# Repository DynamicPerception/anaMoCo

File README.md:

anaMoCo Board
=============

The anaMoCo board is the heart of the [AT<sup>2</sup> two-axis analog controller](http://dynamicperception.com/products/at2-motion-controller)
 sold by Dynamic Perception.

This controller supports control of two DC motors from 6-16V at up to 1.2A each axis.

Key Features
------------

- Control up to two DC motor axes
     - 6-16V power input/output
     - Up to 1.2A per axis
- 99% Analog (one final PWM stage)
     - No microcontroller
- Support for input from a two axis, pot-style joystick and two knobs
- Analog damping support
- Cruise control
- Direction inversion
- Locking DC Jacks

License and Copyright
---------------------

anaMoCo and the AT<sup>2</sup> are Copyright (c) 2012-2013 Dynamic Perception LLC.

All files shared under the Creative Commons Attibution-Share-Alike 3.0 License.

anaMoCo and AT<sup>2</sup> names are trademarks of Dynamic Perception LLC.

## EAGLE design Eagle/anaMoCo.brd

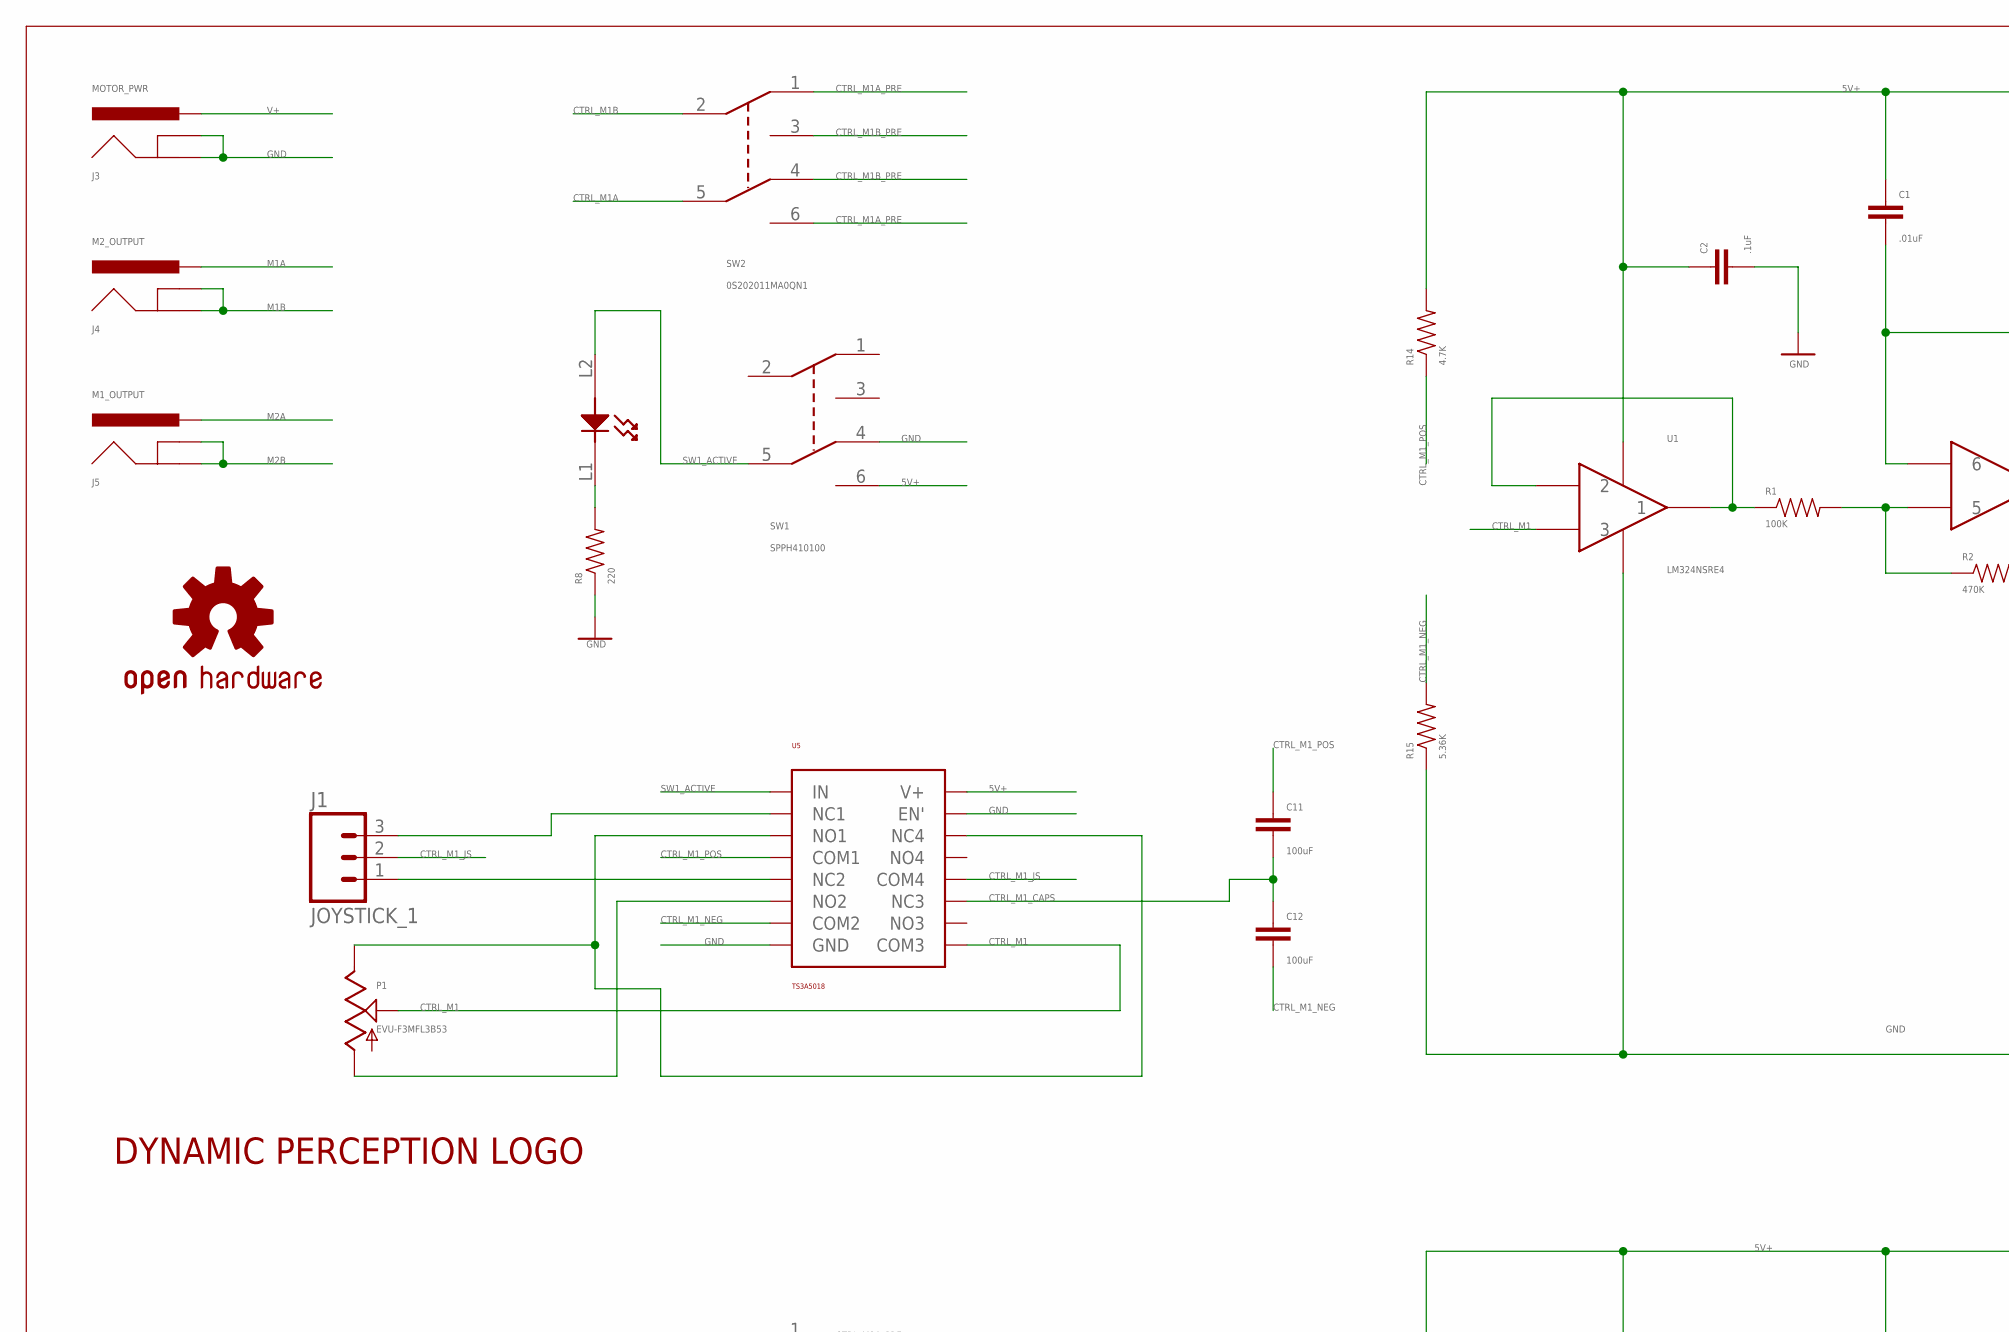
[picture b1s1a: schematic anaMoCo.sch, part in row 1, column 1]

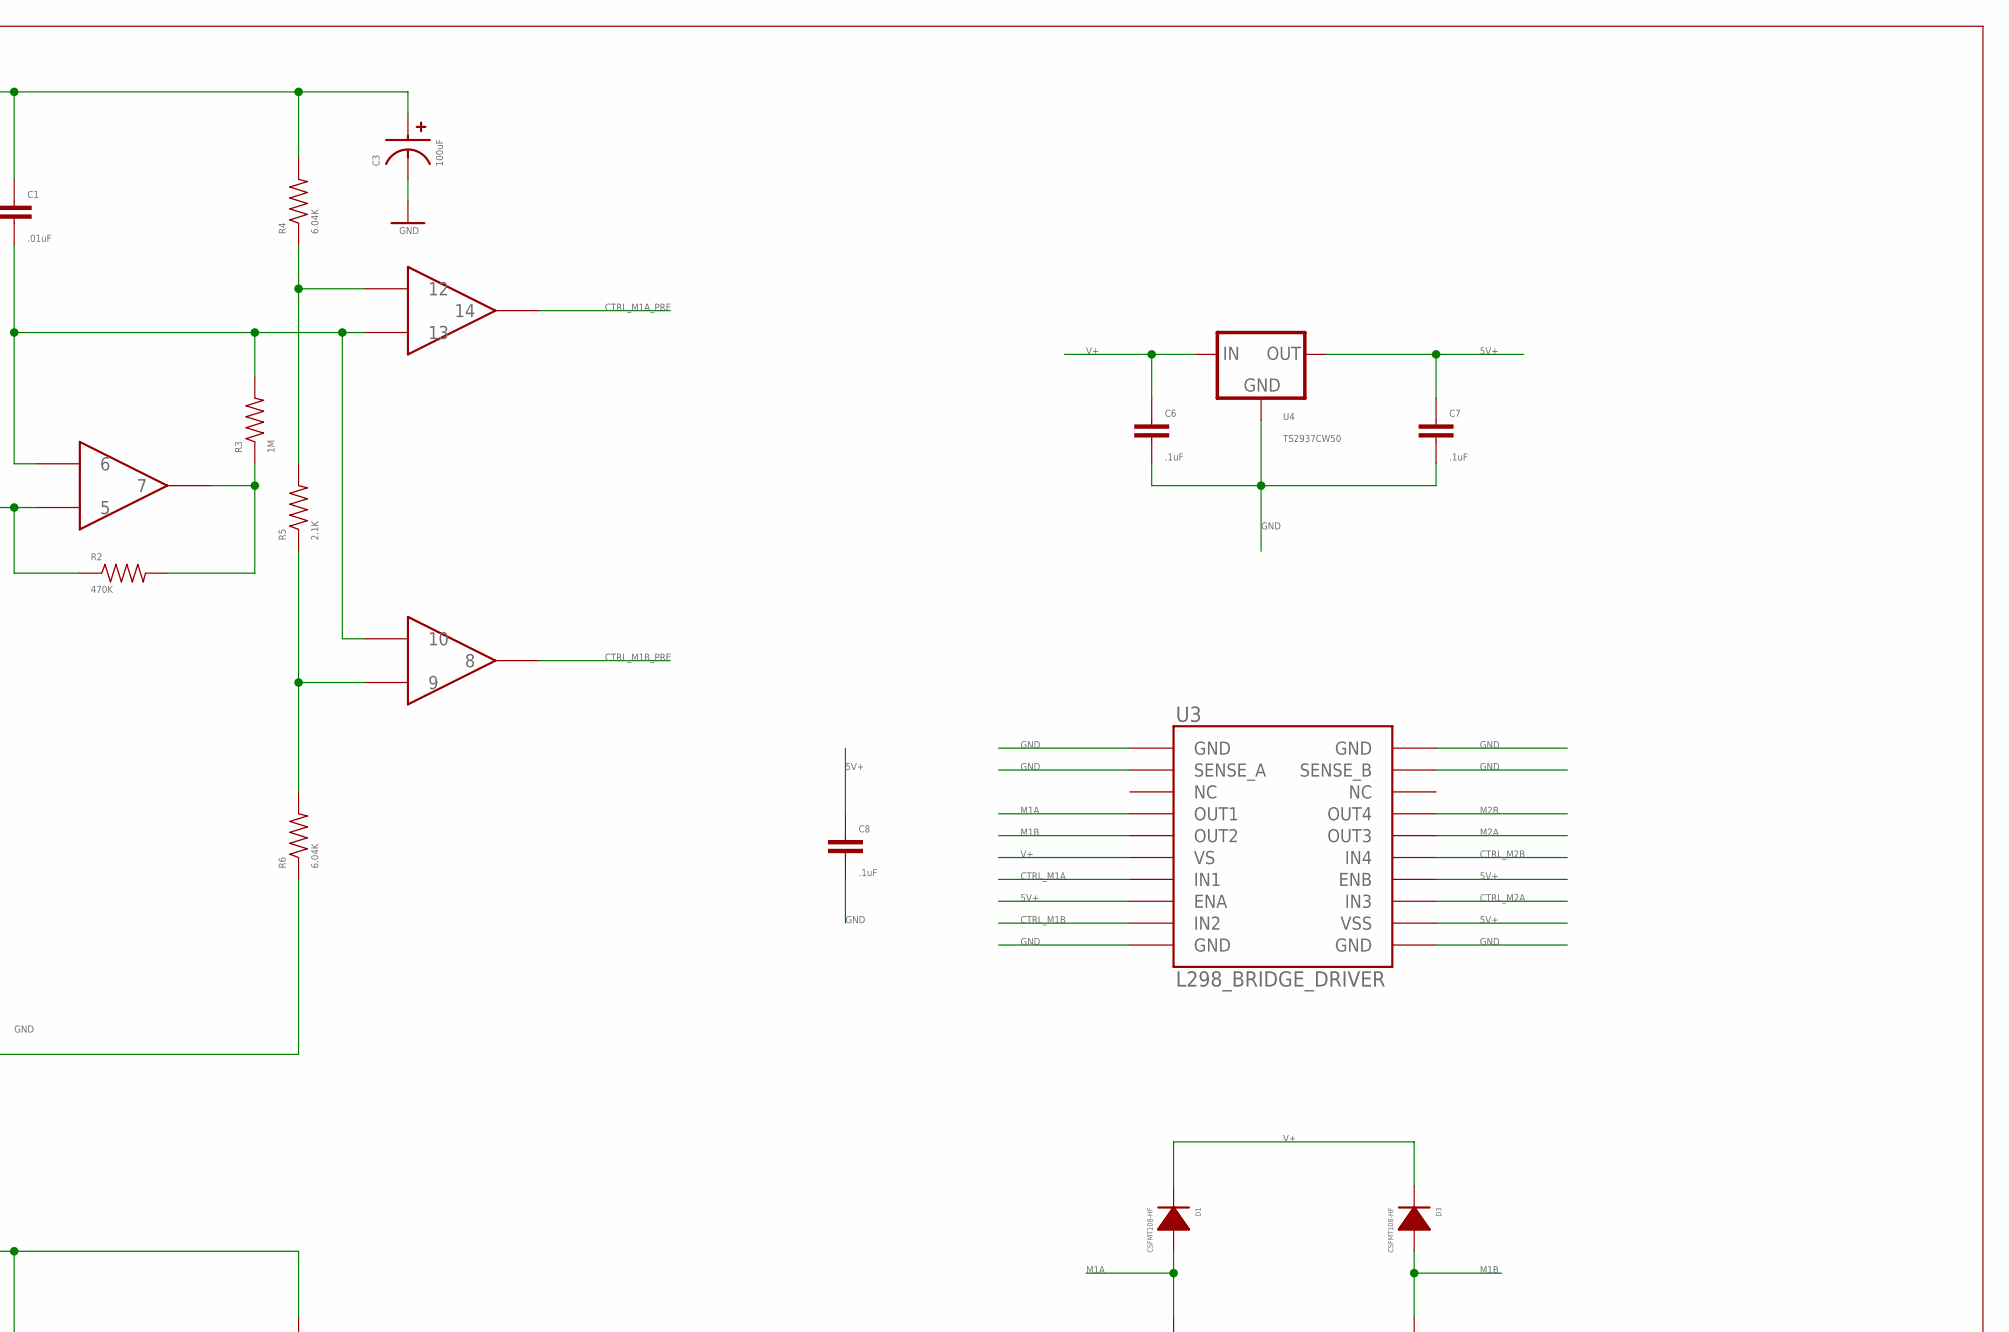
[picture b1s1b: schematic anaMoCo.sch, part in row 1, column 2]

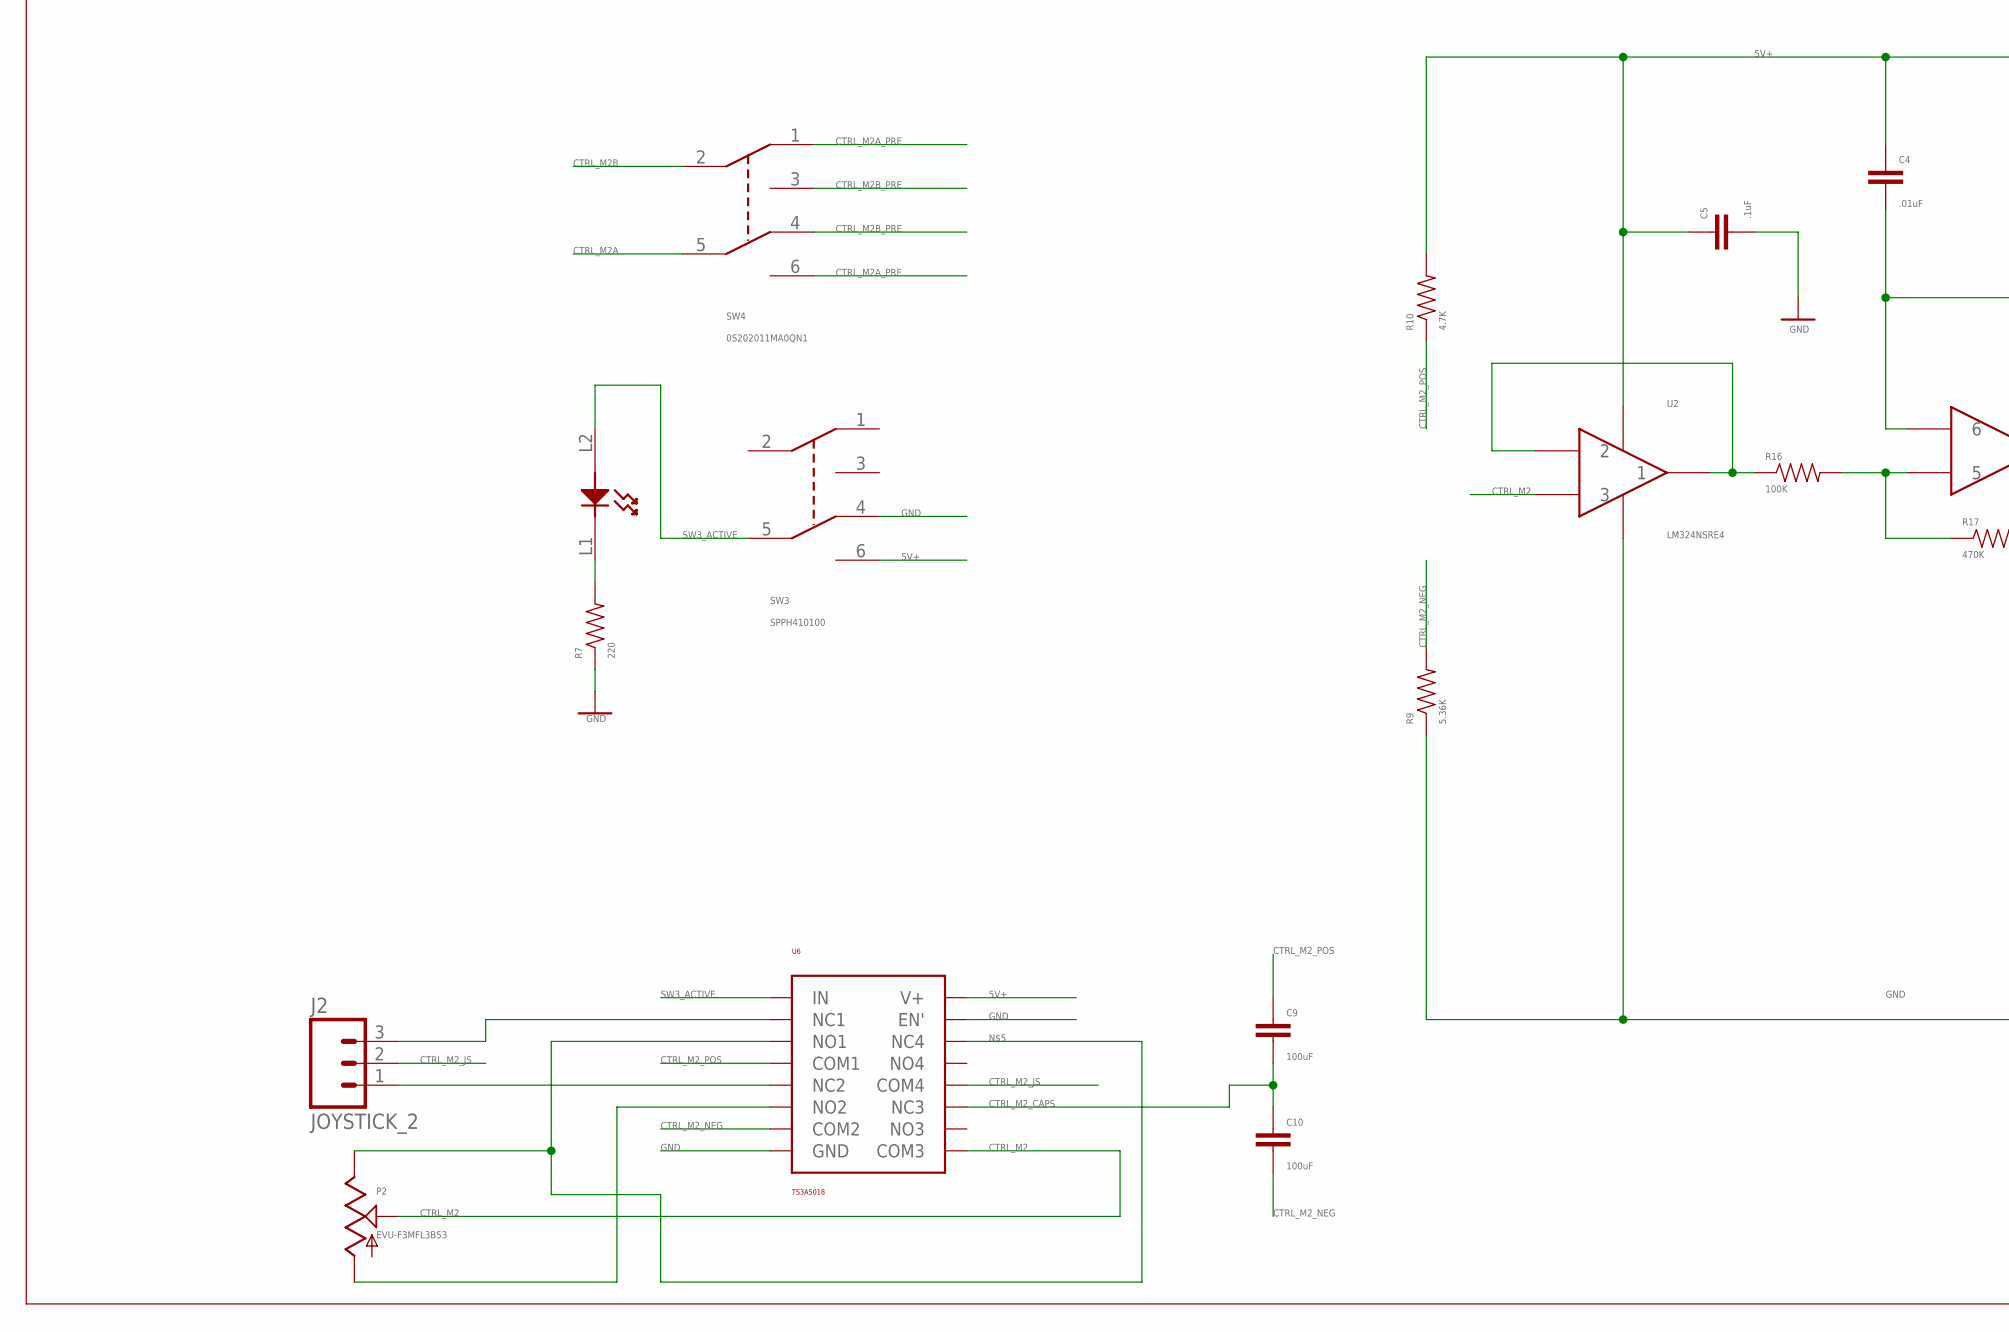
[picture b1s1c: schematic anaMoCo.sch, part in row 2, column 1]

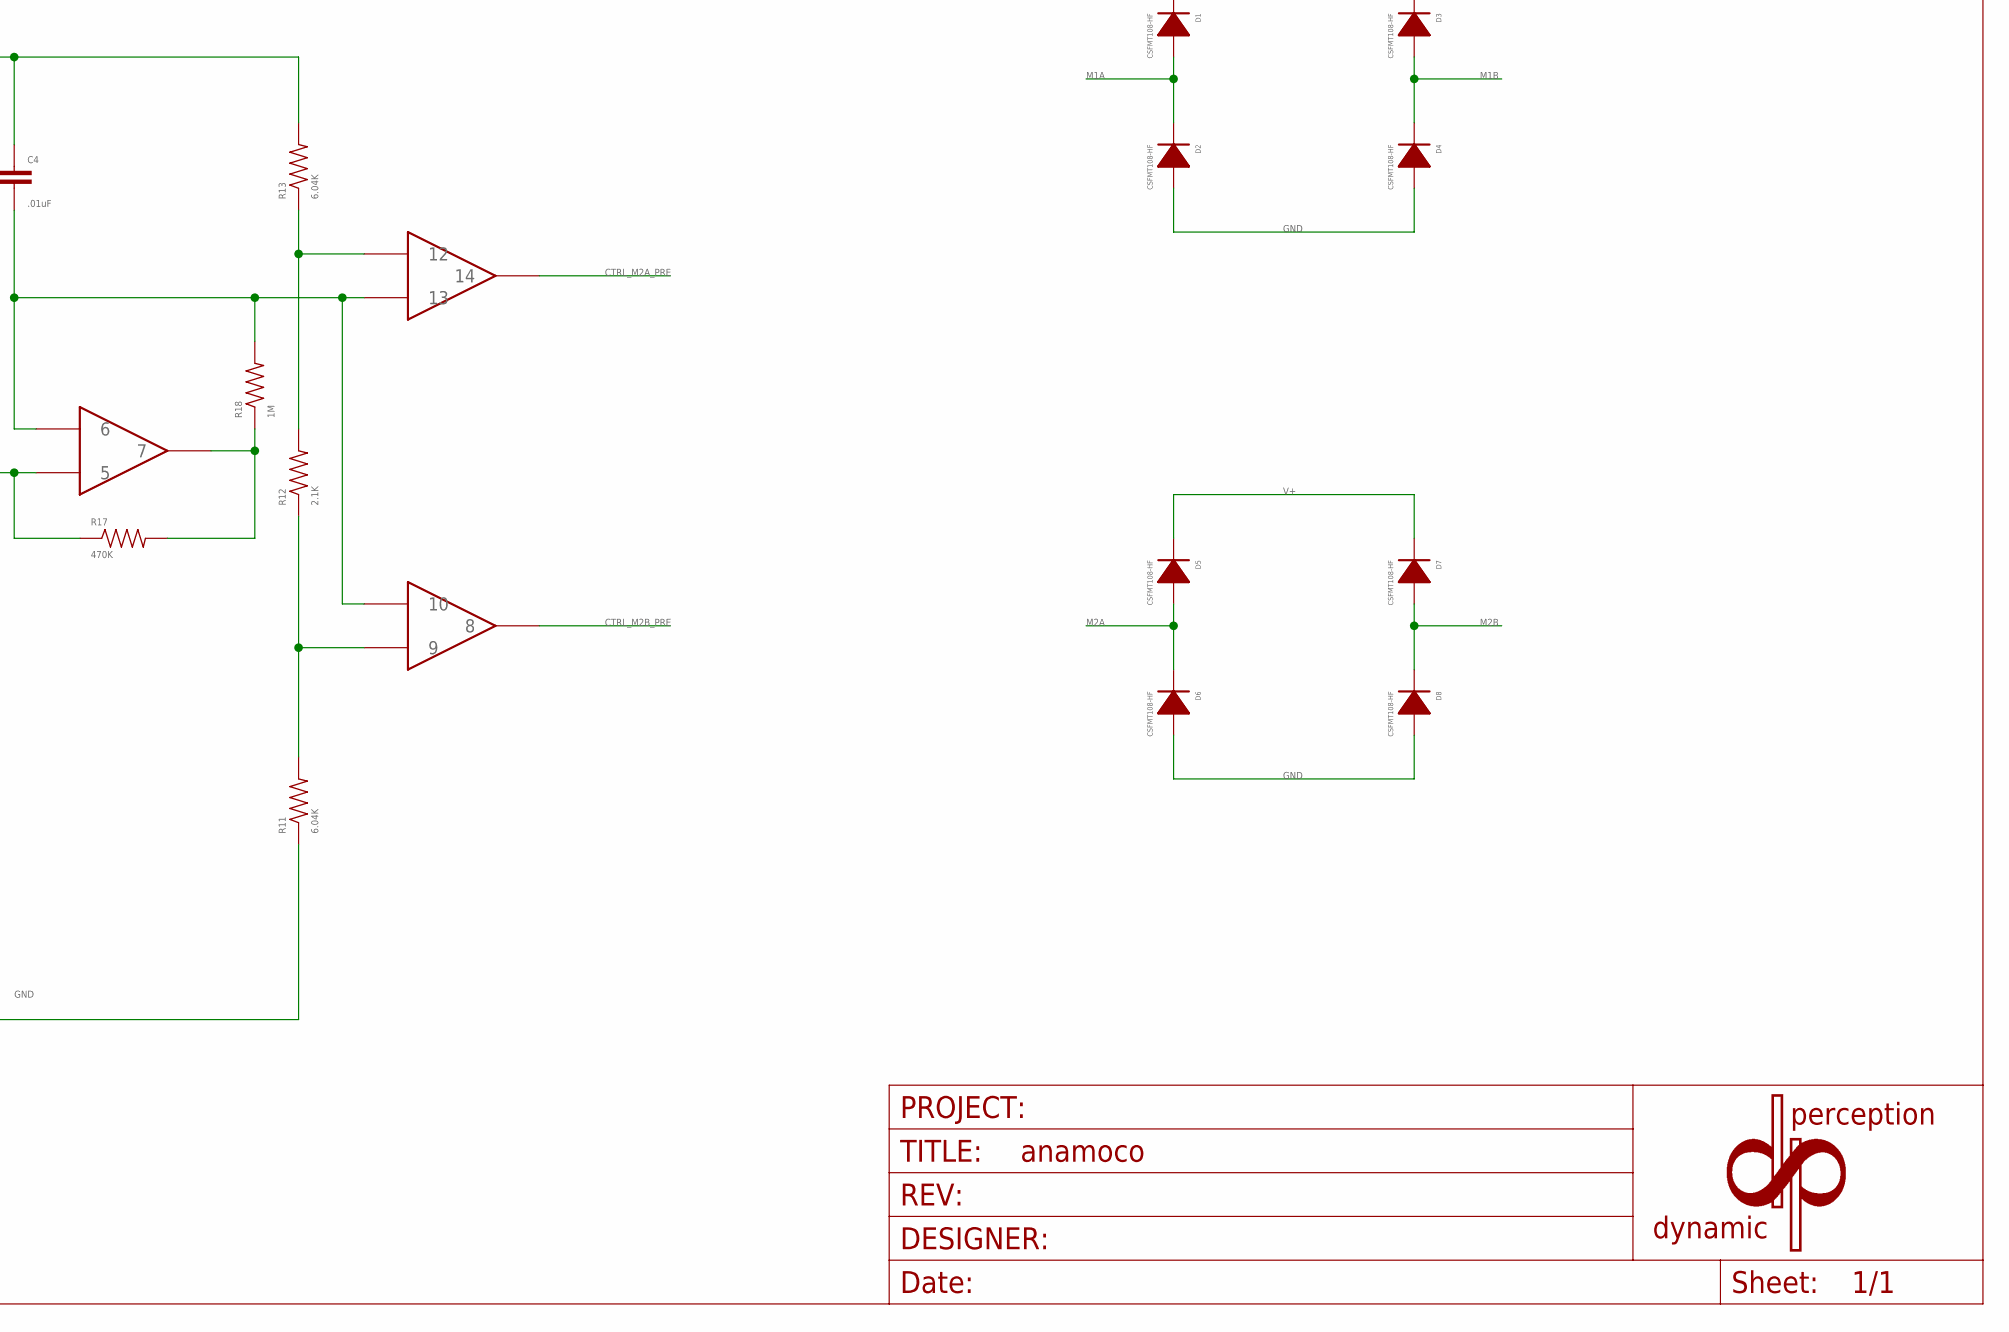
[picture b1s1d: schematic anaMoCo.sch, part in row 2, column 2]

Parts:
C1, C4: .01uF; 0402_CAP
C2, C5, C6, C7, C8: .1uF; 0402_CAP
C3: 100uF; 6.3MM_DIA_CAP_SMD
C9, C10, C11, C12: 100uF; 1206
D1, D2, D3, D4, D5, D6, D7, D8: CSFMT108-HF; SOD-123
J1: JOYSTICK_1; MOLEX-1X3
J2: JOYSTICK_2; MOLEX-1X3
J3: MOTOR_PWR; POWER_JACK_PTH
J4: M2_OUTPUT; POWER_JACK_PTH
J5: M1_OUTPUT; POWER_JACK_PTH
LOGO1: DP_LOGOLARGE; DP_LOGO_LARGE
P1, P2: EVU-F3MFL3B53; PTV09A-4_POT
R1, R16: 100K; 0402_RES
R2, R17: 470K; 0402_RES
R3, R18: 1M; 0402_RES
R4, R6, R11, R13: 6.04K; 0402_RES
R5, R12: 2.1K; 0402_RES
R7, R8: 220; 0402_RES
R9, R15: 5.36K; 0402_RES
R10, R14: 4.7K; 0402_RES
SW1, SW3: SPPH410100; PS004_SW
SW2, SW4: 0S202011MA0QN1; OS202011MA0QN1
U1, U2: LM324NSRE4; SOP-14
U3: L298_BRIDGE_DRIVER; POWERSO20
U4: TS2937CW50; SOT223
U5, U6: TS3A5018; TTSOP-16
U$1: OSHW-LOGOM; OSHW-LOGO-M
U$2: DP_FRAME

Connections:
5V+: C1.1, C2.1, C3.POS, C4.1, C5.1, C7.1, C8.1, R4.2, R10.2, R13.2, R14.2, SW1.6, SW3.6, U1.4, U2.4, U3.8 (ENA), U3.12 (VSS), U3.14 (ENB), U4.3 (OUT), U5.16 (V+), U6.16 (V+)
BIAS2: R5.1, R6.2, U1.9
BIAS4: R11.2, R12.1, U2.9
BLAH: R4.1, R5.2, U1.12
BLAH2: R12.2, R13.1, U2.12
CTRL_M1: P1.2, U1.3, U5.9 (COM3)
CTRL_M1A: SW2.5, U3.7 (IN1)
CTRL_M1A_PRE: SW2.1, SW2.6, U1.14
CTRL_M1B: SW2.2, U3.9 (IN2)
CTRL_M1B_PRE: SW2.3, SW2.4, U1.8
CTRL_M1_CAPS: C11.2, C12.1, U5.11 (NC3)
CTRL_M1_JS: J1.2, U5.12 (COM4)
CTRL_M1_NEG: C12.2, R15.2, U5.7 (COM2)
CTRL_M1_POS: C11.1, R14.1, U5.4 (COM1)
CTRL_M2: P2.2, U2.3, U6.9 (COM3)
CTRL_M2A: SW4.5, U3.13 (IN3)
CTRL_M2A_PRE: SW4.1, SW4.6, U2.14
CTRL_M2B: SW4.2, U3.15 (IN4)
CTRL_M2B_PRE: SW4.3, SW4.4, U2.8
CTRL_M2_CAPS: C9.2, C10.1, U6.11 (NC3)
CTRL_M2_JS: J2.2, U6.12 (COM4)
CTRL_M2_NEG: C10.2, R9.2, U6.7 (COM2)
CTRL_M2_POS: C9.1, R10.1, U6.4 (COM1)
GND: C2.2, C3.NEG, C5.2, C6.2, C7.2, C8.2, D2.ANODE, D4.ANODE, D6.ANODE, D8.ANODE, J3.GND, J3.GNDBREAK, R6.1, R7.1, R8.1, R9.1, R11.1, R15.1, SW1.4, SW3.4, U1.11, U2.11, U3.1 (GND), U3.2 (SENSE_A), U3.10 (GND), U3.11 (GND), U3.19 (SENSE_B), U3.20 (GND), U4.2 (GND), U5.8 (GND), U5.15 (EN'), U6.8 (GND), U6.15 (EN')
M1A: D1.ANODE, D2.CATHODE, J4.PWR, U3.4 (OUT1)
M1B: D3.ANODE, D4.CATHODE, J4.GND, J4.GNDBREAK, U3.5 (OUT2)
M2A: D5.ANODE, D6.CATHODE, J5.PWR, U3.16 (OUT3)
M2B: D7.ANODE, D8.CATHODE, J5.GND, J5.GNDBREAK, U3.17 (OUT4)
unnamed: R1.1, U1.1, U1.2
unnamed: R1.2, R2.1, U1.5
unnamed: R2.2, R3.1, U1.7
unnamed: C1.2, R3.2, U1.6, U1.10, U1.13
unnamed: P2.1, U6.3 (NO1), U6.14 (NC4)
unnamed: P2.3, U6.6 (NO2)
unnamed: R8.2, SW1.L1 (L2)
unnamed: P1.1, U5.3 (NO1), U5.14 (NC4)
unnamed: R7.2, SW3.L1 (L2)
unnamed: J2.3, U6.2 (NC1)
unnamed: J2.1, U6.5 (NC2)
unnamed: J1.3, U5.2 (NC1)
unnamed: J1.1, U5.5 (NC2)
unnamed: R16.1, U2.1, U2.2
unnamed: R16.2, R17.1, U2.5
unnamed: R17.2, R18.1, U2.7
unnamed: C4.2, R18.2, U2.6, U2.10, U2.13
unnamed: P1.3, U5.6 (NO2)
SW1_ACTIVE: SW1.5, SW1.L2 (L1), U5.1 (IN)
SW3_ACTIVE: SW3.5, SW3.L2 (L1), U6.1 (IN)
V+: C6.1, D1.CATHODE, D3.CATHODE, D5.CATHODE, D7.CATHODE, J3.PWR, U3.6 (VS), U4.1 (IN)

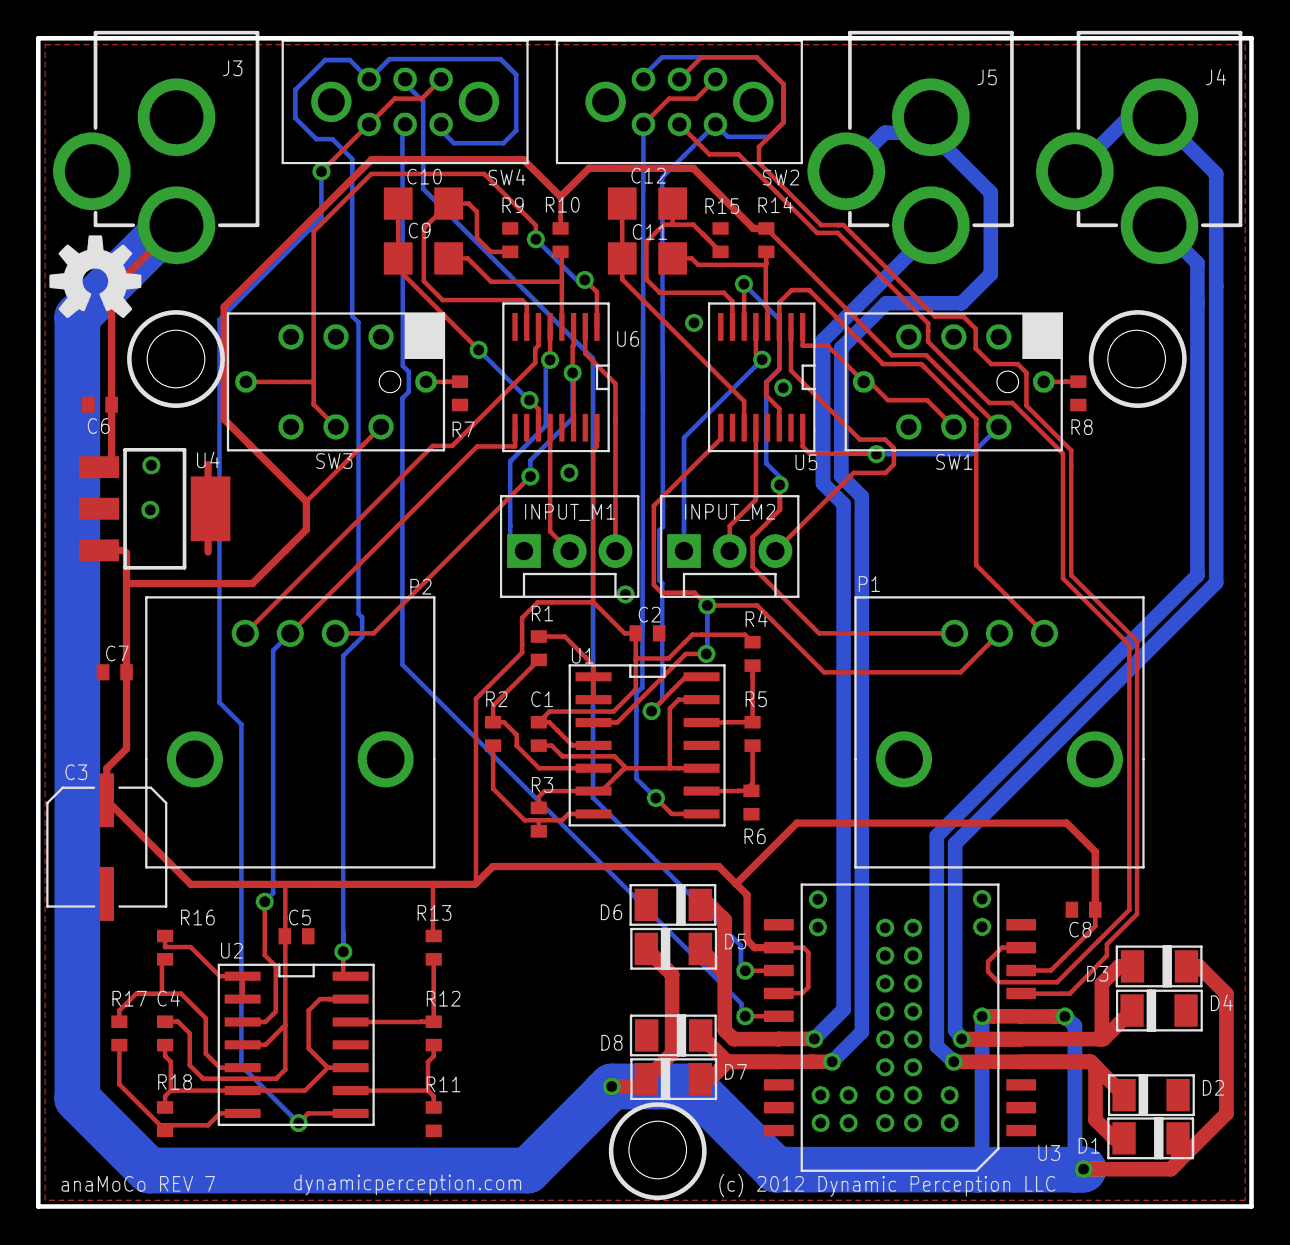
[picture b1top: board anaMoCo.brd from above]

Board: 2 copper layers, 67.4 x 64.9 mm, 58 parts (1 on the bottom side), 49 nets.

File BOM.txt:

Partlist

Exported from joystick_motor_controller.sch at 11/20/2012 9:31:51 AM

EAGLE Version 6.2.0 Copyright (c) 1988-2012 CadSoft

Assembly variant: 

Part     Value              Device                 Package           Library             Sheet

C1       .01uF              CAP_NONPOL0402         0402_CAP          parkers_parts       1
C2       .1uF               CAP_NONPOL0402         0402_CAP          parkers_parts       1
C3       100uF              CAP_POLARIZED6.3MM_SMD 6.3MM_DIA_CAP_SMD parkers_parts       1
C4       .01uF              CAP_NONPOL0402         0402_CAP          parkers_parts       1
C5       .1uF               CAP_NONPOL0402         0402_CAP          parkers_parts       1
C6       .1uF               CAP_NONPOL0402         0402_CAP          parkers_parts       1
C7       .1uF               CAP_NONPOL0402         0402_CAP          parkers_parts       1
C8       .1uF               CAP_NONPOL0402         0402_CAP          parkers_parts       1
C9       100uF              CAP1206                1206              SparkFun-Passives   1
C10      100uF              CAP1206                1206              SparkFun-Passives   1
C11      100uF              CAP1206                1206              SparkFun-Passives   1
C12      100uF              CAP1206                1206              SparkFun-Passives   1
D1       CSFMT108-HF        1N4148WSOD-123         SOD-123           parkers_parts       1
D2       CSFMT108-HF        1N4148WSOD-123         SOD-123           parkers_parts       1
D3       CSFMT108-HF        1N4148WSOD-123         SOD-123           parkers_parts       1
D4       CSFMT108-HF        1N4148WSOD-123         SOD-123           parkers_parts       1
D5       CSFMT108-HF        1N4148WSOD-123         SOD-123           parkers_parts       1
D6       CSFMT108-HF        1N4148WSOD-123         SOD-123           parkers_parts       1
D7       CSFMT108-HF        1N4148WSOD-123         SOD-123           parkers_parts       1
D8       CSFMT108-HF        1N4148WSOD-123         SOD-123           parkers_parts       1
J1       JOYSTICK_1         M03POLAR               MOLEX-1X3         SparkFun-Connectors 1
J2       JOYSTICK_2         M03POLAR               MOLEX-1X3         SparkFun-Connectors 1
J3       MOTOR_PWR          POWER_JACKPTH          POWER_JACK_PTH    SparkFun-Connectors 1
J4       M2_OUTPUT          POWER_JACKPTH          POWER_JACK_PTH    SparkFun-Connectors 1
J5       M1_OUTPUT          POWER_JACKPTH          POWER_JACK_PTH    SparkFun-Connectors 1
P1       EVU-F3MFL3B53      POTENTIOMETERPTV09A-4  PTV09A-4_POT      parkers_parts       1
P2       EVU-F3MFL3B53      POTENTIOMETERPTV09A-4  PTV09A-4_POT      parkers_parts       1
R1       100K               RESISTOR0402           0402_RES          parkers_parts       1
R2       470K               RESISTOR0402           0402_RES          parkers_parts       1
R3       1M                 RESISTOR0402           0402_RES          parkers_parts       1
R4       6.04K              RESISTOR0402           0402_RES          parkers_parts       1
R5       2.1K               RESISTOR0402           0402_RES          parkers_parts       1
R6       6.04K              RESISTOR0402           0402_RES          parkers_parts       1
R7       220                RESISTOR0402           0402_RES          parkers_parts       1
R8       220                RESISTOR0402           0402_RES          parkers_parts       1
R9       5.36K              RESISTOR0402           0402_RES          parkers_parts       1
R10      4.7K               RESISTOR0402           0402_RES          parkers_parts       1
R11      6.04K              RESISTOR0402           0402_RES          parkers_parts       1
R12      2.1K               RESISTOR0402           0402_RES          parkers_parts       1
R13      6.04K              RESISTOR0402           0402_RES          parkers_parts       1
R14      4.7K               RESISTOR0402           0402_RES          parkers_parts       1
R15      5.36K              RESISTOR0402           0402_RES          parkers_parts       1
R16      100K               RESISTOR0402           0402_RES          parkers_parts       1
R17      470K               RESISTOR0402           0402_RES          parkers_parts       1
R18      1M                 RESISTOR0402           0402_RES          parkers_parts       1
SW1      SPPH410100         PS004_SWPS004          PS004_SW          parkers_parts       1
SW2      0S202011MA0QN1     DPDTOS202011MA0QN1     OS202011MA0QN1    parkers_parts       1
SW3      SPPH410100         PS004_SWPS004          PS004_SW          parkers_parts       1
SW4      0S202011MA0QN1     DPDTOS202011MA0QN1     OS202011MA0QN1    parkers_parts       1
U1       LM324NSRE4         LM324SOP-14            SOP-14            parkers_parts       1
U2       LM324NSRE4         LM324SOP-14            SOP-14            parkers_parts       1
U3       L298_BRIDGE_DRIVER L298_BRIDGE_DRIVER     POWERSO20         SparkFun-PowerIC    1
U4       TS2937CW50         V_REG_MIC2920          SOT223            SparkFun-PowerIC    1
U5       TS3A5018           TS3A5018TTSOP-16       TTSOP-16          parkers_parts       1
U6       TS3A5018           TS3A5018TTSOP-16       TTSOP-16          parkers_parts       1

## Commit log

2013-03-28 * Added all files
2013-03-28 * Fixed name in license file

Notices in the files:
Eagle/anaMoCo.brd:
(c) 2012 Dynamic Perception LLC
parts and their libraries:
SparkFun-Connectors: Licensing: CC v3.0 Share-Alike You are welcome to use this library for commercial purposes.
